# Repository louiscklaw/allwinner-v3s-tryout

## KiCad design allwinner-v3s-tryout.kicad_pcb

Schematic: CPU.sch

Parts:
C1, C11, C14, C19, C25, C27, C28, C30, C34, C43, C48, C50, C51, C52, C54, C55, C58: C106; C_0603_1608Metric_Pad1.05x0.95mm_HandSolder
C2, C3, C6, C17, C18, C22, C23, C24, C26, C29, C32, C33, C36, C37, C38, C39, C40, C41, C42, C46, C47, C57, C60, C62, C63, C66: C104; C_0603_1608Metric_Pad1.05x0.95mm_HandSolder
C4: C102; C_0603_1608Metric_Pad1.05x0.95mm_HandSolder
C5, C15, C16, C20, C21, C31, C35, C44, C45, C59: C105; C_0603_1608Metric_Pad1.05x0.95mm_HandSolder
C7, C8, C12, C13, C49, C53, C56: C18pf; C_0603_1608Metric_Pad1.05x0.95mm_HandSolder
C9: C106-50v; C_1206_3216Metric_Pad1.42x1.75mm_HandSolder
C10: C104-50v; C_1206_3216Metric_Pad1.42x1.75mm_HandSolder
C61, C65: C33pf; C_0603_1608Metric_Pad1.05x0.95mm_HandSolder
C64: C101; C_0603_1608Metric_Pad1.05x0.95mm_HandSolder
D1: SD_1N5819_S4; D_SOD-123F
J1, J2: Conn_01x30; Pin_Header_Straight_1x30_Pitch1.27mm
J3: Conn_01x24; TE_2-84953-4_1x24-1MP_P1.0mm_Horizontal
L1, L2, L3, L4: L_2.2uH; inductor_smd_3x1.4mm
L5: L_10uH; inductor_smd_3x1.4mm
MK1: Microphone; Pin_Header_Straight_1x02_Pitch2.54mm
R1, R5, R6, R7, R8, R9, R10: R473; R_0603_1608Metric_Pad1.05x0.95mm_HandSolder
R2: R241; R_0603_1608Metric_Pad1.05x0.95mm_HandSolder
R3: R602; R_0603_1608Metric_Pad1.05x0.95mm_HandSolder
R4: R104; R_0603_1608Metric_Pad1.05x0.95mm_HandSolder
R11: R106; R_0603_1608Metric_Pad1.05x0.95mm_HandSolder
R12, R14, R37: R103; R_0603_1608Metric_Pad1.05x0.95mm_HandSolder
R13: R5R1; R_0603_1608Metric_Pad1.05x0.95mm_HandSolder
R15: R0; R_0603_1608Metric_Pad1.05x0.95mm_HandSolder
R16: R204; R_0603_1608Metric_Pad1.05x0.95mm_HandSolder
R17, R18, R25, R26, R27, R28, R30, R34: R202; R_0603_1608Metric_Pad1.05x0.95mm_HandSolder
R19, R21, R23: R684; R_0603_1608Metric_Pad1.05x0.95mm_HandSolder
R20, R22, R24: R154; R_0603_1608Metric_Pad1.05x0.95mm_HandSolder
R29, R31, R32, R33: R510; R_0603_1608Metric_Pad1.05x0.95mm_HandSolder
R35: R682; R_0603_1608Metric_Pad1.05x0.95mm_HandSolder
R36: R822; R_0603_1608Metric_Pad1.05x0.95mm_HandSolder
R38: R113; R_0603_1608Metric_Pad1.05x0.95mm_HandSolder
SW1, SW2, SW3, SW4: SW_Push; SW_SPST_PTS645
U1: USB_MICRO; PinHeader_1x05_P2.54mm_Vertical
U2: NS2009; MSOP-10_3x3mm_P0.5mm
U3: FC-40P-LCD; HIROSE_FH12S-40S-0.5SH(55)
U4: allwinner-V3S-eLQFP128; v3s-elqfp128
U5: TF_CARD; SUNTECH_ST-TF-003A
U6: MC-146; Crystal_SMD_SeikoEpson_MC146-4Pin_6.7x1.5mm_HandSoldering
U7: MX25L12835F; SOIC-8_3.9x4.9mm_P1.27mm
U8: PT4101; SOT-23-6_Handsoldering
U9: XT_3225; Crystal_SMD_SeikoEpson_TSX3225-4Pin_3.2x2.5mm_HandSoldering
U10: GD5F1GQ4UAYIG; SOIC-8_3.9x4.9mm_P1.27mm
U11: EA3036; QFN-24-1EP_3x3mm_P0.4mm_EP1.75x1.6mm_ThermalVias
U12: XC6206; SOT-23_Handsoldering
U13: HR911105A; HANRUN_HR911105A

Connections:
+1V2: C14.1, C15.1, C16.1, C17.1, C18.1, C19.1, C20.1, C21.1, C22.1, C23.1, C24.1, J2.11, U4.19 (VDD-SYS3), U4.20 (VDD-CPU3), U4.21 (VDD-CPU2), U4.25 (VDD-CPU1), U4.26 (VDD-CPU0), U4.38 (VDD-CPU4), U4.47 (VDD-CPU5), U4.51 (VDD-CPU6), U4.56 (VDD-CPU7), U4.58 (VDD-SYS4), U4.64 (VDD-SYS5), U4.80 (VDD-SYS0), U4.88 (EPHY-VDD), U4.108 (VDD-SYS1), U4.126 (VDD-SYS2)
+1V8: C32.2, C43.1, C44.1, C45.1, C46.1, C47.1, J2.13, R17.2, U4.59 (VCC-DRAM8), U4.60 (VCC-DRAM9), U4.61 (VCC-DRAM10), U4.62 (VCC-DRAM11), U4.65 (VCC-DRAM0), U4.66 (VCC-DRAM1), U4.67 (VCC-DRAM2), U4.68 (VCC-DRAM3), U4.69 (VCC-DRAM4), U4.70 (VCC-DRAM5), U4.72 (VCC-DRAM6), U4.79 (VCC-DRAM7)
+3V0: C28.1, C29.1, C41.1, C57.1, C58.1, C59.1, J1.29, R4.1, R30.2, U4.76 (VCC-PLL), U4.115 (AVCC), U12.2 (Vout)
+3V3: C3.2, C6.1, C34.1, C35.1, C36.1, C37.1, C38.1, C39.1, C42.1, C48.1, C49.1, C52.1, C53.1, C55.1, C56.1, J1.16, J2.15, J3.2, L2.1, L3.1, L4.1, L5.1, R1.2, R5.1, R6.1, R7.1, R8.1, R9.1, R10.1, R14.1, R15.2, R19.1, R21.1, R23.1, R25.1, R26.1, R27.1, R28.1, U2.1 (VDD), U3.4 (VCC), U3.31 (DISP), U4.12 (VCC-PE0), U4.29 (VCC-PE1), U4.50 (VCC-IO3), U4.57 (VCC-IO2), U4.85 (VCC-MCSI), U4.93 (EPHY-VCC), U4.104 (VCC-IO0), U4.109 (VCC-USB), U4.122 (HPVCCIN), U4.127 (VCC-IO1), U5.4 (VDD), U7.3 (~WP~), U7.7 (~HOLD~), U7.8 (VCC), U10.3 (~WP~), U10.7 (~HOLD~), U10.8 (VCC), U12.3 (Vin)
+5V: C1.1, C2.1, C11.1, C50.2, C51.2, C54.2, J2.30, J3.1, L1.1, U1.1 (VCC), U8.6 (IN), U11.7 (VIN2), U11.8 (EN2), U11.9 (EN1), U11.10 (VIN1), U11.16 (VIN3), U11.18 (EN3)
/CPU/CSI_SCK: U4.9 (PE21/CSI_SCK/TWI1_SCK/UART1_TX)
/CPU/CSI_SDA: U4.8 (PE22/CSI_SDA/TWI1_SDA/UART1_RX)
/CPU/MCSI_MCLK: J2.5, U4.10 (PE20/CSI_FIELD/CSI_MIPI_MCLK)
/CPU/MCSI_PWDN: U4.4 (PG1/SDC1_CMD/PG_EINT1)
/CPU/MCSI_RST: U4.5 (PG0/SDC1_CLK/PG_EING0)
/CPU/PENIRQ: U2.7 (PENIRQ)
ETH_LED_LINK: U4.77 (EPHY-LINK-LED)
ETH_LED_SPD: U4.78 (EPHY-SPD-LED)
ETH_RX_N: J1.27, R33.1, U4.89 (EPHY-RXN), U13.6 (RD-)
ETH_RX_P: J1.25, R32.1, U4.90 (EPHY-RXP), U13.3 (RD+)
ETH_TX_N: J1.23, R31.1, U4.91 (EPHY-TXN), U13.2 (TD-)
ETH_TX_P: J1.21, R29.1, U4.92 (EPHY-TXP), U13.1 (TD+)
HBIAS: J1.9, U4.119 (HBIAS)
HP_COM: J1.1, U4.125 (HPCOM)
HP_COMFB: J1.3, U4.124 (HPCOMFB)
HP_L: J1.5, U4.121 (HPOUTL)
HP_R: J1.7, U4.120 (HPOUTR)
KEYADC0: C4.1, J1.18, R4.2, R35.2, U4.112 (LRDAC0)
LCD_CLK: J2.3, J3.21, U3.30 (CLK), U4.37 (PE0/CSI_PCLK/LCD_CLK)
LCD_D2: J3.14, U3.23 (B2), U4.33 (PE4/CSI_D0/LCD_D2)
LCD_D3: J3.15, U3.24 (B3), U4.32 (PE5/CSI_D1/LCD_D3)
LCD_D4: J3.12, U3.25 (B4), U4.31 (PE6/CSI_D2/LCD_D4)
LCD_D5: J3.13, U3.26 (B5), U4.30 (PE7/CSI_D3/LCD_D5)
LCD_D6: J3.10, U3.27 (B6), U4.28 (PE8/CSI_D4/LCD_D6)
LCD_D7: J3.11, U3.28 (B7), U4.27 (PE9/CSI_D5/LCD_D7)
LCD_D10: J3.8, U3.15 (G2), U4.24 (PE10/CSI_D6/LCD_D10)
LCD_D11: J3.9, U3.16 (G3), U4.23 (PE11/CSI_D7/LCD_D11)
LCD_D12: J3.6, U3.17 (G4), U4.22 (PE12/CSI_D8/LCD_D12)
LCD_D13: J3.7, U3.18 (G5), U4.18 (PE13/CSI_D9/LCD_D13)
LCD_D14: J3.4, U3.19 (G6), U4.17 (PE14/CSI_D10/LCD_D14)
LCD_D15: J3.5, U3.20 (G7), U4.16 (PE15/CSI_D11/LCD_D15)
LCD_D18: J3.22, U3.7 (R2), U4.15 (PE16/CSI_D12/LCD_D18)
LCD_D19: U3.8 (R3), U4.14 (PE17/CSI_D13/LCD_D19)
LCD_D20: U3.9 (R4), U4.13 (PE18/CSI_D14/LCD_D20)
LCD_D21: U3.10 (R5), U4.11 (PE19/CSI_D15/LCD_D21)
LCD_D22: U3.11 (R6), U4.7 (PE23/LCD_D22)
LCD_D23: U3.12 (R7), U4.6 (PE24/LCD_D23)
LCD_DE: J2.1, J3.20, U3.34 (DEN), U4.36 (PE1/CSI_MCLK/LCD_DE)
LCD_HSYNC: J3.17, U3.32 (HSYNC), U4.35 (PE2/CSI_HSYNC/LCD_HSYNC)
LCD_VSYNC: J3.16, U3.33 (VSYNC), U4.34 (PE3/CSI_VSYNC/LCD_VSYNC)
MCSI_CK_N: J2.27, U4.87 (MCSI-CKN)
MCSI_CK_P: J2.25, U4.86 (MCSI-CKP)
MCSI_D0_N: J2.19, U4.82 (MCSI-D0N)
MCSI_D0_P: J2.17, U4.81 (MCSI-D0P)
MCSI_D1_N: J2.23, U4.84 (MCSI-D1N)
MCSI_D1_P: J2.21, U4.83 (MCSI-D1P)
MIC_N: C66.1, J1.11, U4.114 (MICIN1N)
MIC_P: C62.1, J1.13, U4.113 (MICI1P)
unnamed: C53.2, R21.2, R22.2, U11.3 (FB2)
unnamed: C56.2, R23.2, R24.2, U11.2 (FB3)
unnamed: C60.1, L5.2, R29.2, R31.2, U13.4 (TCT)
unnamed: C61.1, C62.2, C64.1, MK1.2 (+), R30.1
unnamed: C63.1, R32.2, R33.2, U13.5 (TCT)
unnamed: C64.2, C65.1, C66.2, MK1.1 (-), R34.1
unnamed: D1.2 (A), L1.2, U8.1 (SW)
unnamed: L2.2, U11.11 (SW1)
unnamed: L3.2, U11.6 (SW2)
unnamed: L4.2, U11.20 (SW3)
unnamed: R3.2, U4.94 (EPHY-RTX)
unnamed: R17.1, R18.2
unnamed: R35.1, R36.2, SW1.1
unnamed: R36.1, R37.2, SW2.1
unnamed: R37.1, R38.2, SW3.1
unnamed: R38.1, SW4.1
PB2: J2.7, U4.41 (PB2/UART2_RTS/PB_EINT2)
PB3: J2.9, U4.42 (PB3/UART2_CTS/PB_EINT3)
PB4: J2.10, R12.1, U4.43 (PB4/PWM0/PB_EINT4), U8.4 (EN)
PB5: J2.12, U4.44 (PB5/PWM1/PB_EINT5)
RESET: C5.1, R10.2, U4.99 (RESET)
SDC0_CLK: J1.24, U4.105 (PF2/SDC0_CLK/UART0_TX), U5.5 (CLK)
SDC0_CMD: J1.26, R7.2, U4.103 (PF3/SDC0_CMD/JTAG_DO1), U5.3 (CMD/MOSI)
SDC0_D0: J1.22, R6.2, U4.106 (PF1/SDC0_D0/JTAG_DI1), U5.7 (DAT0/MISO)
SDC0_D1: J1.20, R5.2, U4.107 (PF0/SDC0_D1/JTAG_MS1), U5.8 (DAT1)
SDC0_D2: J1.30, R9.2, U4.101 (PF5/SDC0_D2/JTAG_CK1), U5.1 (DAT2)
SDC0_D3: J1.28, R8.2, U4.102 (PF4/SDC0_D3/UART0_RX), U5.2 (DAT3/CS)
SDC1_D0: J1.6, U4.3 (PG2/SDC1_D0/PG_EINT2)
SDC1_D1: J1.8, U4.2 (PG3/SDC1_D1/PG_EINT3)
SDC1_D2: J1.10, U4.1 (PG4/SDC1_D2/PG_EINT4)
SDC1_D3: J1.12, U4.128 (PG5/SDC1_D3/PG_EINT5)
SPI_CS: J2.28, R14.2, U4.54 (PC2/SDC2_RST/SPI_CS), U7.1 (~CS~), U10.1 (~CS~)
SPI_MISO: J2.26, U4.52 (PC0/SDC2_CLK/SPI_MISO), U7.2 (SO), U10.2 (SO)
SPI_MOSI: J2.24, U4.55 (PC3/SDC2_D0/SPI_MOSI), U7.5 (SI), U10.5 (SI)
SPI_SCK: J2.22, U4.53 (PC1/SDC2_CMD/SPI_CLK), U7.6 (CLK), U10.6 (CLK)
SVREF: C32.1, C33.2, U4.63 (SVREF1), U4.71 (SVREF0)
SZQ: R2.2, U4.73 (SZQ)
TPX1: U2.2 (XP), U3.37 (XR)
TPX2: U2.4 (XN), U3.39 (XL)
TPY1: U2.3 (YP), U3.38 (YD)
TPY2: U2.5 (YN), U3.40 (YU)
TWI0_SCK: J2.14, R28.2, U2.10 (SCL), U4.45 (PB6/TWI0_SCK/PB_EINT6)
TWI0_SDA: J2.16, R27.2, U2.9 (SDA), U4.46 (PB7/TWI0_SDA/PB_EINT7)
TWI1_SCK: J3.19, R26.2, U4.48 (PB8/TWI1_SCK/UART0_TX/PB_EINT8)
TWI1_SDA: J3.18, R25.2, U4.49 (PB9/TWI1_SCA/UART0_RX/PB_EINT9)
UART2_RX: J2.8, U4.40 (PB1/UART2_RX/PB_EINT1)
UART2_TX: J2.6, U4.39 (PB0/UART2_TX/PB_EINT0)
USB_ID: J1.19, R1.1, U1.4 (ID), U4.100 (PF6)
USB_N: J1.17, U1.2 (D-), U4.110 (USB-DM)
USB_P: J1.15, U1.3 (D+), U4.111 (USB-DP)
VLED+: C9.1, C10.1, D1.1 (K), U3.2 (LEDA), U8.5 (OV)
VLED-: R13.1, U3.1 (LEDK), U8.3 (FB)
VRA1: C31.1, U4.117 (VRA1)
VRA2: C30.1, R16.1, U4.118 (VRA2)
Vhp_bp: C25.1, C26.1, U4.123 (HPVCCBP)
Vrtc: C40.1, R15.1, U4.98 (VCC-RTC-)
Vrtc_io: C27.1, U4.97 (RTC-VIO)
X24MIN: C13.2, U4.75 (X24MIN), U9.4 (GND)
X24MOUT: C12.1, U4.74 (X24MOUT), U9.2 (GND)
X32KIN: C8.2, R11.2, U4.96 (X32KIN), U6.2 (XIN)
X32KOUT]: C7.2, R11.1, U4.95 (X32KOUT), U6.1 (XOUT)

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
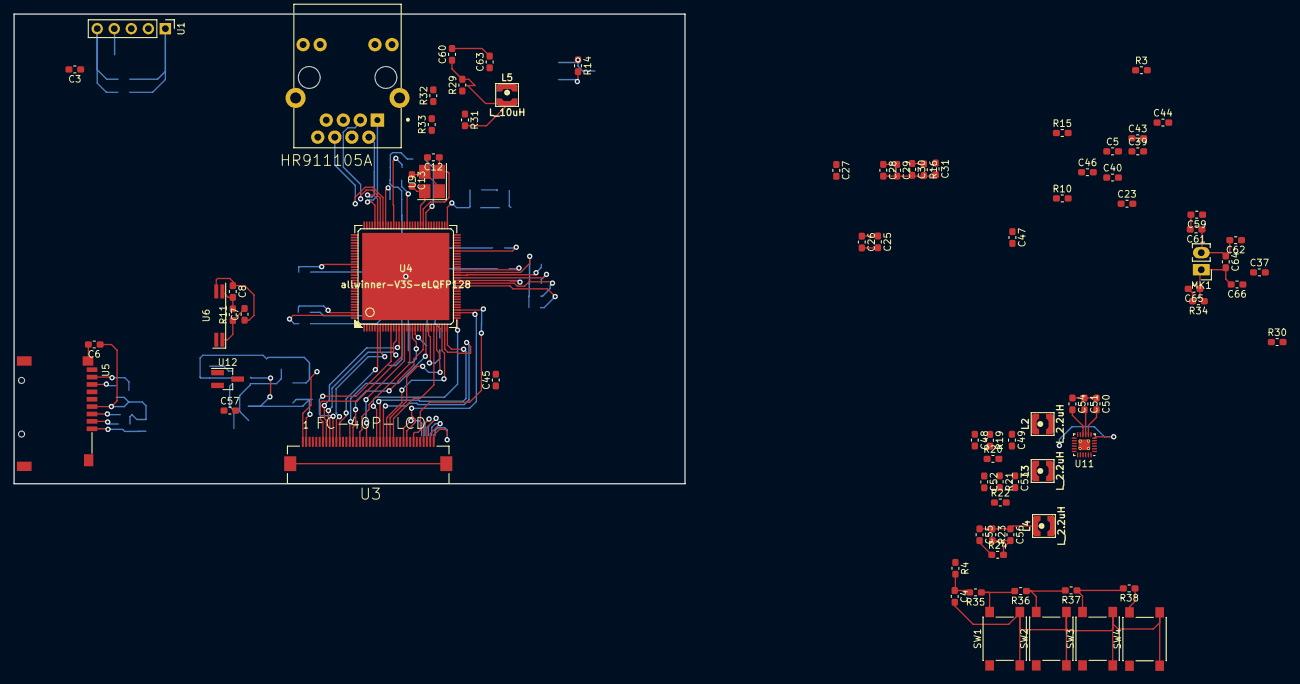
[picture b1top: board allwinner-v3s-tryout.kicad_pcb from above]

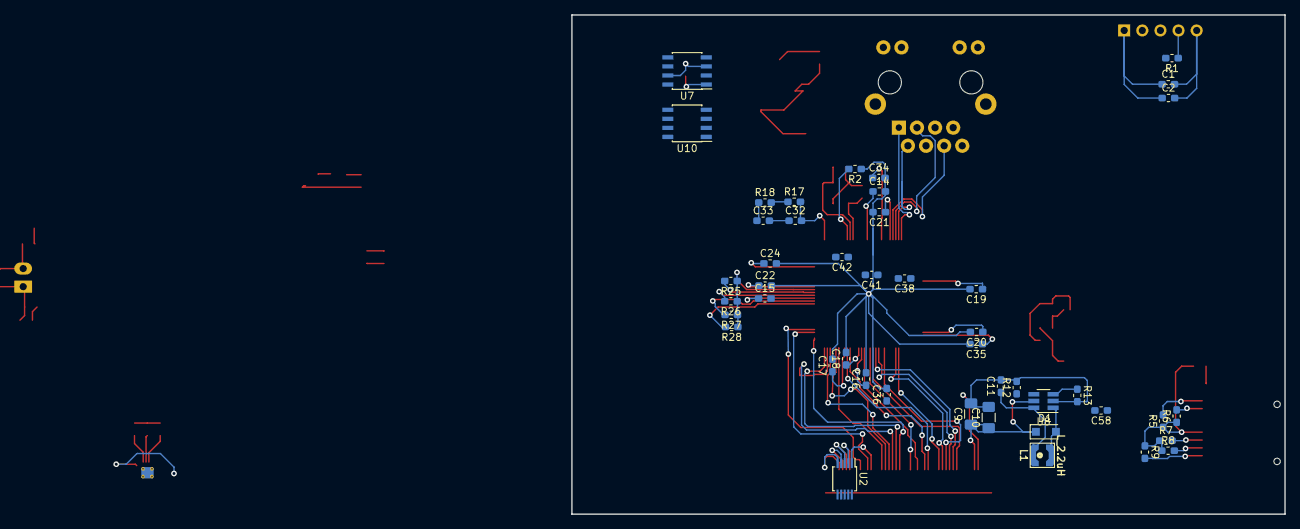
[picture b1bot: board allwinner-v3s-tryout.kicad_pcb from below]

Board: 2 copper layers, 100.0 x 70.0 mm, 128 parts (45 on the bottom side), 88 nets.

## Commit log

2018-10-21 update,
2018-10-30 update with ref/project,
2020-05-05 ci: init travis build config,
2020-05-05 ci: init travis token,
